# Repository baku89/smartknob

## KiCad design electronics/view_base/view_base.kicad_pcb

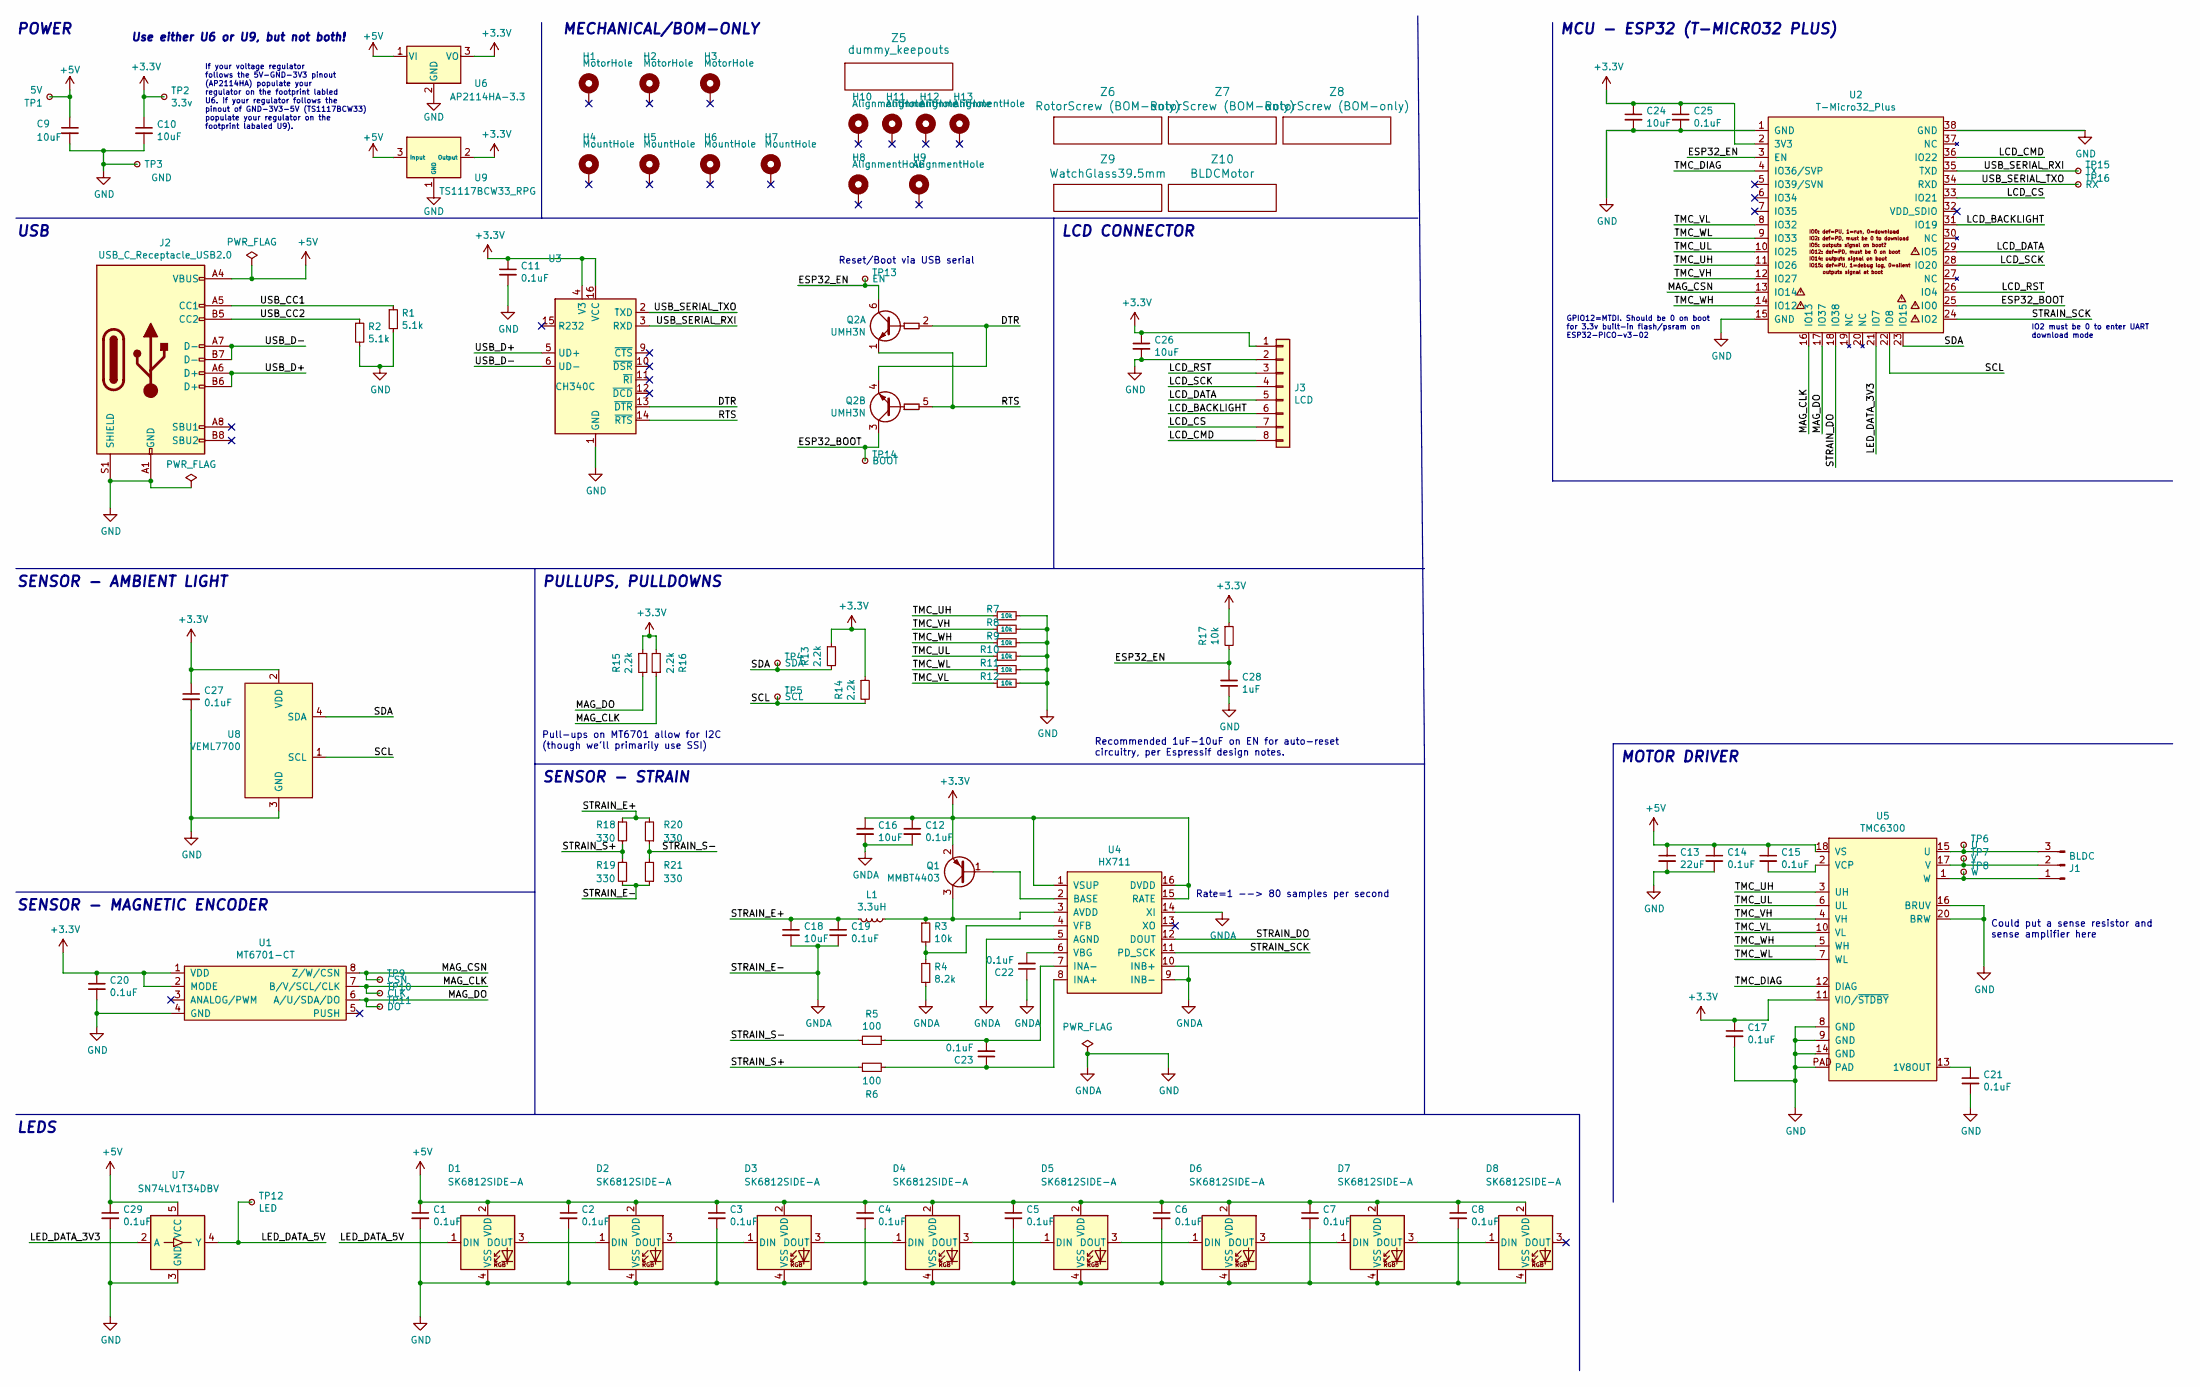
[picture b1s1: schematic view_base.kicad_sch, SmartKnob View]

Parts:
C1, C2, C3, C4, C5, C6, C7, C8, C11, C12, C14, C15, C17, C19, C20, C21, C22, C23, C25, C27, C29: 0.1uF; C_0603_1608Metric; LCSC C1591
C9, C10, C16, C18, C24, C26: 10uF; C_0805_2012Metric; LCSC C15850
C13: 22uF; C_0805_2012Metric; LCSC C98190
C28: 1uF; C_0603_1608Metric; Mouser 187-CL10A105KA8NNNC
D1, D2, D3, D4, D5, D6, D7, D8: SK6812SIDE-A; SK6812-SIDE-A; Digikey 1528-4691-ND
H1, H2, H3: MotorHole; MountingHole_M1.6; LCSC C2931389
H4, H5, H6, H7: MountHole; MountingHole_2.2mm_M2_ISO7380_Pad_NonVirtual; LCSC C2911210 or C2911532 (screw), C2961595 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
H8, H9, H10, H11, H12, H13: AlignmentHole; MountingHole_2.2mm_M2_ISO7380_Pad_NonVirtual
J1: BLDC; 532610371; LCSC C293630
J2: USB_C_Receptacle_USB2.0; USB4510_NoPaste; LCSC C428463
J3: LCD; SolderPads_2mm_8
L1: 3.3uH; L_0805_2012Metric; LCSC C307744
Q1: MMBT4403; SOT-23; LCSC C78864
Q2: UMH3N; SOT-363_SC-70-6; LCSC C62892
R1, R2: 5.1k; R_0603_1608Metric; LCSC C105580
R3, R7, R8, R9, R10, R11, R12, R17: 10k; R_0603_1608Metric; LCSC C98220
R4: 8.2k; R_0603_1608Metric; LCSC C114637
R5, R6: 100; R_0603_1608Metric; LCSC C319953
R13, R14, R15, R16: 2.2k; R_0603_1608Metric; LCSC C4190
R18, R19, R20, R21: 330; R_2512_6332Metric; LCSC C19866
TP1: 5V; TestPoint_Pad_D2.0mm_ValueSilk
TP2: 3.3v; TestPoint_Pad_D2.0mm_ValueSilk
TP3: GND; TestPoint_Pad_D2.0mm_ValueSilk
TP4: SDA; TestPoint_Pad_D2.0mm_ValueSilk
TP5: SCL; TestPoint_Pad_D2.0mm_ValueSilk
TP6: U; TestPoint_Pad_D2.0mm_ValueSilk
TP7: V; TestPoint_Pad_D2.0mm_ValueSilk
TP8: W; TestPoint_Pad_D2.0mm_ValueSilk
TP9: CSN; TestPoint_Pad_D2.0mm_ValueSilk
TP10: CLK; TestPoint_Pad_D2.0mm_ValueSilk
TP11: DO; TestPoint_Pad_D2.0mm_ValueSilk
TP12: LED; TestPoint_Pad_D2.0mm_ValueSilk
TP13: EN; TestPoint_Pad_D2.0mm_ValueSilk
TP14: BOOT; TestPoint_Pad_D2.0mm_ValueSilk
TP15: TX; TestPoint_Pad_D2.0mm_ValueSilk
TP16: RX; TestPoint_Pad_D2.0mm_ValueSilk
U1: MT6701-CT; SOIC-8_3.9x4.9mm_P1.27mm; LCSC C2856764, or C3003196
U2: T-Micro32_Plus; T-Micro32; Digikey N/A
U3: CH340C; SOIC-16_3.9x9.9mm_P1.27mm; LCSC C84681
U4: HX711; SOIC-16_3.9x9.9mm_P1.27mm; LCSC C43656
U5: TMC6300; QFN-20-1EP_3x3mm_P0.4mm_EP1.65x1.65mm_ThermalVias_LargerVia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; Digikey TMC6300-LA-T
U6: AP2114HA-3.3; SOT-223-3_TabPin2_InGndOut; LCSC C460314
U7: SN74LV1T34DBV; SOT-23-5; LCSC C100024
U8: VEML7700; VEML7700-TOP; Digikey VEML7700-TT
U9: TS1117BCW33_RPG; SOT-223-3_TabPin2_GndOutIn; LCSC C6186, C35879, or others
Z5: dummy_keepouts; ViewKeepouts3d
Z6, Z7, Z8: RotorScrew (BOM-only); bom_only_no_pin
Z9: WatchGlass39.5mm; bom_only_no_pin
Z10: BLDCMotor; bom_only_no_pin

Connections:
+3V3: C10.1, C11.1, C12.1, C16.1, C17.1, C20.1, C24.1, C25.1, C26.1, C27.1, J3.1, Q1.2 (E), R13.1, R14.1, R15.1, R16.2, R17.1, TP2.1, U1.1 (VDD), U1.2 (MODE), U2.2 (3V3), U3.4 (V3), U3.16 (VCC), U4.1 (VSUP), U4.15 (RATE), U4.16 (DVDD), U5.11 (VIO/~STDBY), U6.3 (VO), U8.2 (VDD), U9.2 (Output)
+5V: C1.1, C2.1, C3.1, C4.1, C5.1, C6.1, C7.1, C8.1, C9.1, C13.1, C14.1, C15.1, C29.1, D1.2 (VDD), D2.2 (VDD), D3.2 (VDD), D4.2 (VDD), D5.2 (VDD), D6.2 (VDD), D7.2 (VDD), D8.2 (VDD), J2.A4 (VBUS), J2.A9 (VBUS), J2.B4 (VBUS), J2.B9 (VBUS), TP1.1, U5.18 (VS), U6.1 (VI), U7.5 (VCC), U9.3 (Input)
/DTR: Q2.2 (B1), Q2.4 (E2), U3.13 (~DTR)
/ESP32_BOOT: Q2.3 (C2), TP14.1, U2.25 (IO0)
/ESP32_EN: C28.1, Q2.6 (C1), R17.2, TP13.1, U2.3 (EN)
/LCD_BACKLIGHT: J3.6, U2.31 (IO19)
/LCD_CMD: J3.8, U2.36 (IO22)
/LCD_CS: J3.7, U2.33 (IO21)
/LCD_DATA: J3.5, U2.29 (IO5)
/LCD_RST: J3.3, U2.26 (IO4)
/LCD_SCK: J3.4, U2.28 (IO20)
/LED_DATA_3V3: U2.21 (IO7), U7.2 (A)
/LED_DATA_5V: D1.1 (DIN), TP12.1, U7.4 (Y)
/MAG_CLK: R16.1, TP10.1, U1.7 (B/V/SCL/CLK), U2.16 (IO13)
/MAG_CSN: TP9.1, U1.8 (Z/W/CSN), U2.13 (IO14)
/MAG_DO: R15.2, TP11.1, U1.6 (A/U/SDA/DO), U2.17 (IO37)
/RTS: Q2.1 (E1), Q2.5 (B2), U3.14 (~RTS)
/SCL: R14.2, TP5.1, U2.22 (IO8), U8.1 (SCL)
/SDA: R13.2, TP4.1, U2.23 (IO15), U8.4 (SDA)
/STRAIN_DO: U2.18 (IO38), U4.12 (DOUT)
/STRAIN_E+: C18.1, C19.1, L1.2, R18.1, R20.2
/STRAIN_S+: R6.1, R18.2, R19.1
/STRAIN_S-: R5.2, R20.1, R21.2
/STRAIN_SCK: U2.24 (IO2), U4.11 (PD_SCK)
/TMC_DIAG: U2.4 (IO36/SVP), U5.12 (DIAG)
/TMC_UH: R7.1, U2.11 (IO26), U5.3 (UH)
/TMC_UL: R10.1, U2.10 (IO25), U5.6 (UL)
/TMC_VH: R8.1, U2.12 (IO27), U5.4 (VH)
/TMC_VL: R12.1, U2.8 (IO32), U5.10 (VL)
/TMC_WH: R9.1, U2.14 (IO12), U5.5 (WH)
/TMC_WL: R11.1, U2.9 (IO33), U5.7 (WL)
/USB_CC1: J2.A5 (CC1), R1.1
/USB_CC2: J2.B5 (CC2), R2.1
/USB_D+: J2.A6 (D+), J2.B6 (D+), U3.5 (UD+)
/USB_D-: J2.A7 (D-), J2.B7 (D-), U3.6 (UD-)
/USB_SERIAL_RXI: TP15.1, U2.35 (TXD), U3.3 (RXD)
/USB_SERIAL_TXO: TP16.1, U2.34 (RXD), U3.2 (TXD)
GND: C1.2, C2.2, C3.2, C4.2, C5.2, C6.2, C7.2, C8.2, C9.2, C10.2, C11.2, C12.2, C13.2, C14.2, C16.2, C17.2, C18.2, C19.2, C20.2, C21.2, C22.1, C24.2, C25.2, C26.2, C27.2, C28.2, C29.2, D1.4 (VSS), D2.4 (VSS), D3.4 (VSS), D4.4 (VSS), D5.4 (VSS), D6.4 (VSS), D7.4 (VSS), D8.4 (VSS), J2.A1 (GND), J2.A12 (GND), J2.B1 (GND), J2.B12 (GND), J2.S1 (SHIELD), J3.2, R1.2, R2.2, R4.2, R7.2, R8.2, R9.2, R10.2, R11.2, R12.2, R19.2, R21.1, TP3.1, U1.4 (GND), U2.1 (GND), U2.15 (GND), U2.38 (GND), U3.1 (GND), U4.5 (AGND), U4.9 (INB-), U4.10 (INB+), U4.14 (XI), U5.8 (GND), U5.9 (GND), U5.14 (GND), U5.16 (BRUV), U5.20 (BRW), U5.PAD, U6.2 (GND), U7.3 (GND), U8.3 (GND), U9.1 (GND)
unnamed: D1.3 (DOUT), D2.1 (DIN)
unnamed: D2.3 (DOUT), D3.1 (DIN)
unnamed: D3.3 (DOUT), D4.1 (DIN)
unnamed: D4.3 (DOUT), D5.1 (DIN)
unnamed: D5.3 (DOUT), D6.1 (DIN)
unnamed: D6.3 (DOUT), D7.1 (DIN)
unnamed: D7.3 (DOUT), D8.1 (DIN)
unnamed: J1.1, TP8.1, U5.1 (W)
unnamed: J1.2, TP7.1, U5.17 (V)
unnamed: J1.3, TP6.1, U5.15 (U)
unnamed: Q1.1 (B), U4.2 (BASE)
unnamed: L1.1, Q1.3 (C), R3.1, U4.3 (AVDD)
unnamed: C23.1, R6.2, U4.8 (INA+)
unnamed: C23.2, R5.1, U4.7 (INA-)
unnamed: C22.2, U4.6 (VBG)
unnamed: R3.2, R4.1, U4.4 (VFB)
unnamed: C21.1, U5.13 (1V8OUT)
unnamed: C15.2, U5.2 (VCP)

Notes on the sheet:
POWER
Could put a sense resistor and sense amplifier here
MCU - ESP32 (T-MICRO32 PLUS)
If your voltage regulator follows the 5V-GND-3V3 pinout (AP2114HA) populate your regulator on the footprint labled U6. If your regulator follows the pinout of GND-3V3-5V (TS1117BCW33) populate your regulator on the footprint labaled U9).
SENSOR - MAGNETIC ENCODER
MOTOR DRIVER
MECHANICAL/BOM-ONLY
IO2 must be 0 to enter UART download mode
GPIO12=MTDI. Should be 0 on boot for 3.3v built-in flash/psram on ESP32-PICO-v3-02
Pull-ups on MT6701 allow for I2C (though we'll primarily use SSI)
Use either U6 or U9, but not both!
Rate=1 --> 80 samples per second
SENSOR - AMBIENT LIGHT
Recommended 1uF-10uF on EN for auto-reset circuitry, per Espressif design notes.
USB
SENSOR - STRAIN
LEDS
PULLUPS, PULLDOWNS
LCD CONNECTOR
Reset/Boot via USB serial

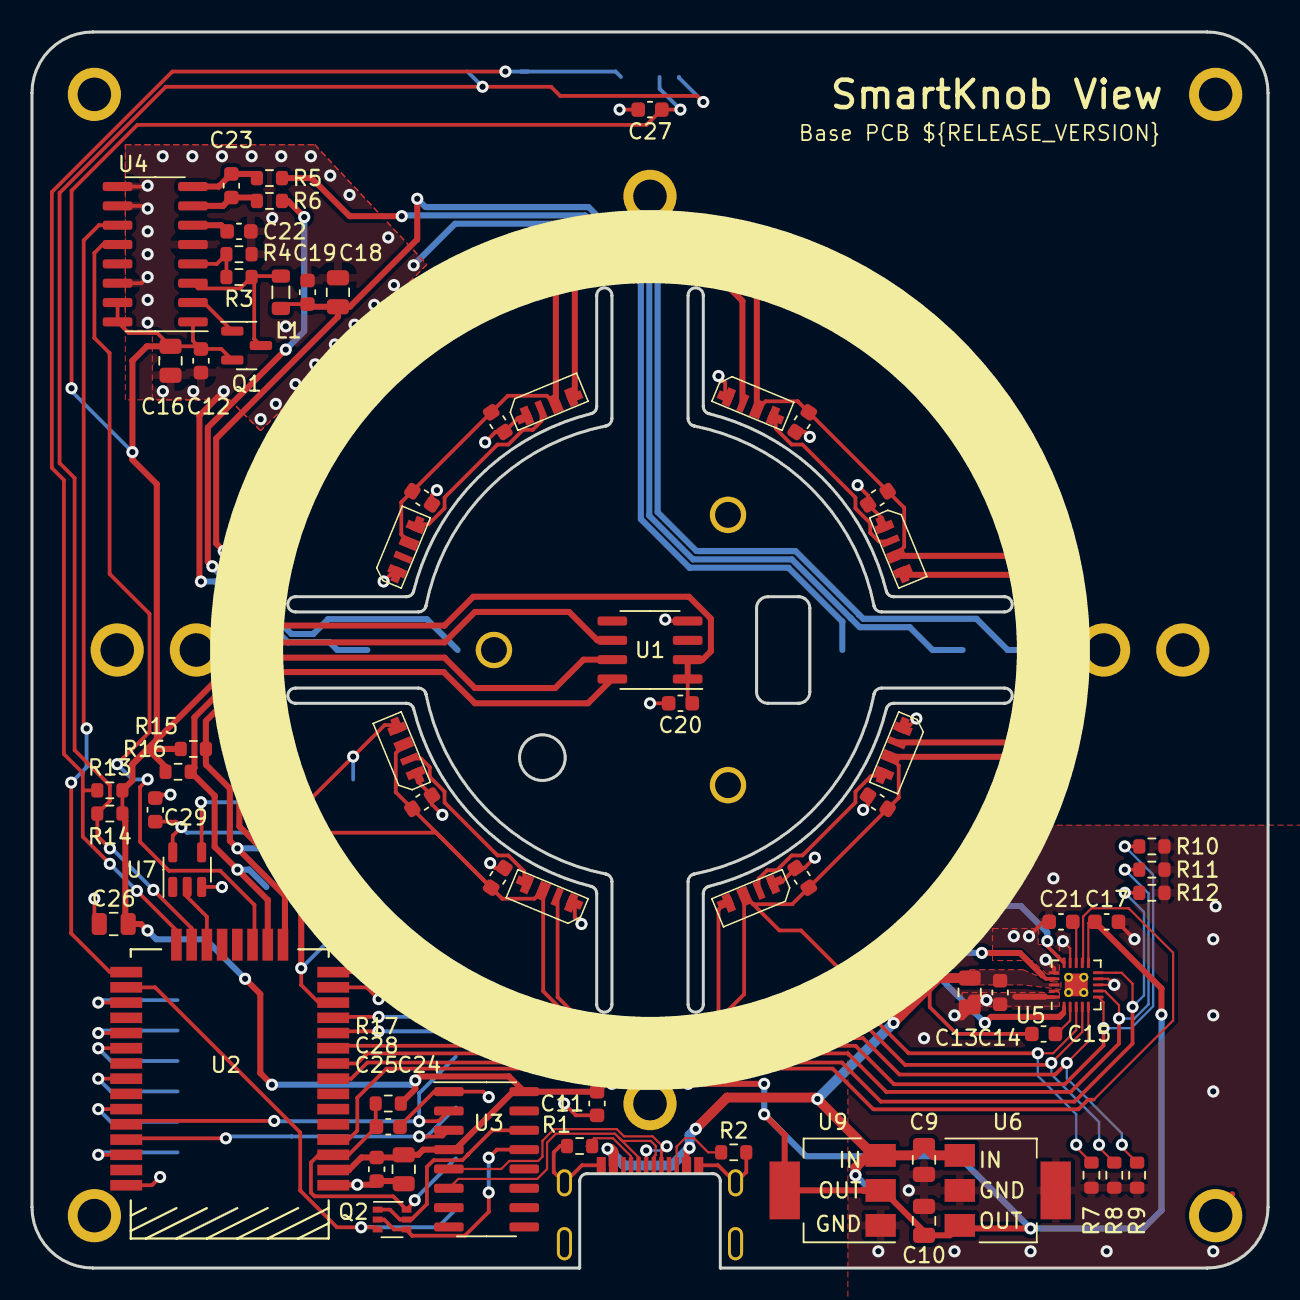
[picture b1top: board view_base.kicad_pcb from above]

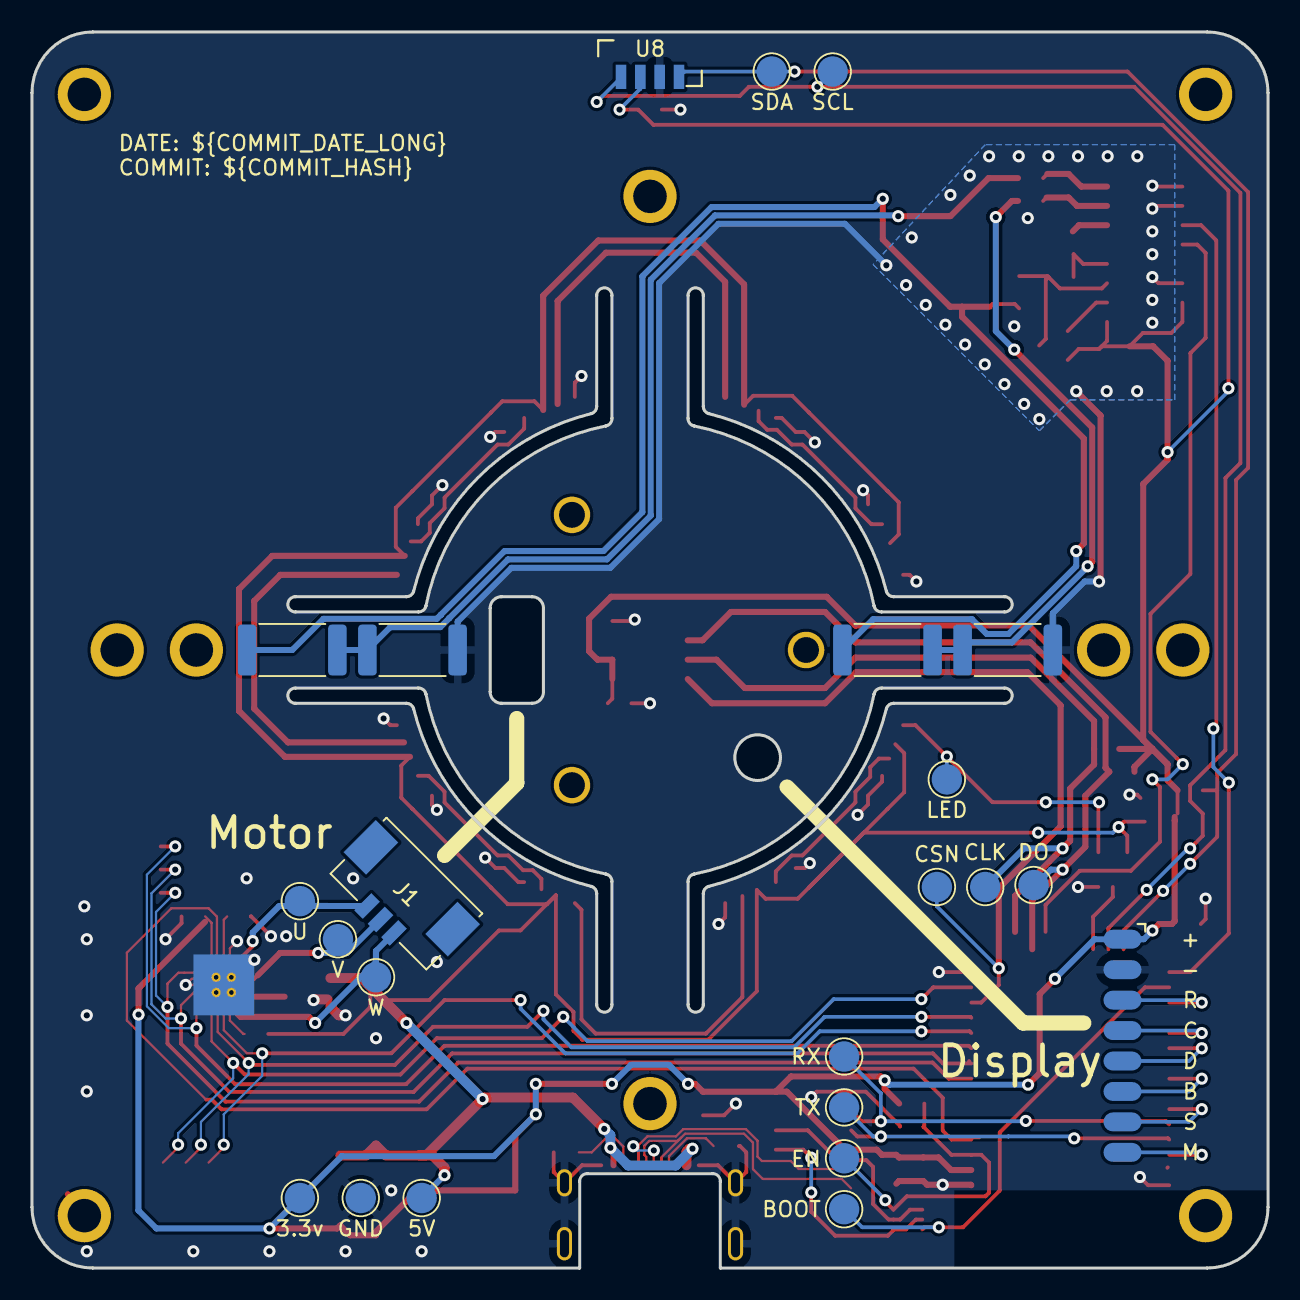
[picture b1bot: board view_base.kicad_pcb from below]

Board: 2 copper layers, 81.2 x 81.2 mm, 108 parts (23 on the bottom side), 56 nets.

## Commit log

2024-01-27 Add courtyards for some SMD parts
2024-01-27 Organize the base PCB for group buy
2024-01-27 Use KiCad 7.0 for GitHub workflow
2024-01-27 Revert the silkscreen for PCB versioning
2024-01-27 Upgrade Kikit to v1.4.0 to support KiCad 7.0
2024-01-27 Ignore some unnecessary DRC rules
2024-01-27 Remove exclude edge layer option in pcb_util.py
2024-01-27 Configure export options for JLCPCB
2024-01-27 Configure Platform.IO for baku89's environment
2024-01-28 Add torque multipliers for BLDC to limit current
2024-01-28 Add 'any' type annotation explicitly to smartknobjs-node
2024-01-28 Add baudRate options to SmartKnobCore and its subclasses
2024-01-28 Add eslint-config-prettier to the local package example-webserial-basic
2024-01-28 Add 'prepare' script to the packges in NPM workspace
2024-01-28 Set the torque weak
2024-01-28 Make the lights monochrome
2024-01-28 Upgrade serialport to 12.0.0 in NPM packages
2024-01-28 Format tscnofig.json in example-cli
2024-01-28 Use baudRate 115200
2024-01-28 Reflect the state.config.position_offset_radians in the LCD
2024-01-28 Add position_offset_radians and position_text to the SmartKnobConfig protobuf
2024-01-28 Implement fillFan method for TFT_eSprite
2024-01-28 Update demo configs based on the new SmartKnobConfig interface
2024-01-28 Add inputs for newly added SmartKnobConfig (position_offset_radians, position_text, and meter_type)
2024-01-28 Replace uint16 led_hue with uint32 base_color in SmartKnobConfig protobuf
2024-01-28 Refactor the code to draw the text for current position
2024-01-28 Reflect state.config.position_text in the LCD
2024-01-28 Switch a meter based on state.config.meter_type
2024-01-28 Tint the 8 LEDs based on config.base_color
2024-01-28 Update the docstring and maxlen of position_text in SmartKnobConfig
2024-01-28 Rewrite led_hue field in configs with 24-bit hex color
2024-01-28 Add meter_type field to SmartKnobConfig protobuf
2024-01-28 Add baseColor input in example-webserial-basic
2024-01-28 Add comments
2024-01-28 Use config.base_color for the meter display
2024-01-28 Add meter_center field to the SmartKnobConfig protobuf
2024-01-28 Fill the LCD black instead of purple on successfully started
2024-01-29 Add new field corresponding to meter_center to sample configs
2024-01-29 Use radians()
2024-01-29 Draw meters considering meter_center
2024-01-29 Use baudRate 1000000
2024-01-29 Add meterCenter field
2024-01-29 Stringify the hex color code correctly
2024-01-29 Add presets
2024-01-29 Switch presets on pressing the knob
2024-02-08 Change the baudRate to 250000
2024-03-29 Fix example
2024-04-04 Tweak the FW configs
2024-04-04 Update the example configs

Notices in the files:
parts and their libraries:
Copyright 2021 Accelerated Designs. All rights reserved.
